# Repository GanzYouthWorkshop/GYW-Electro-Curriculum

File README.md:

# GYW-Electro-Curriculum
Electronic curriculum and oher simple circuits for the Ganz Youth Workshop electric group.

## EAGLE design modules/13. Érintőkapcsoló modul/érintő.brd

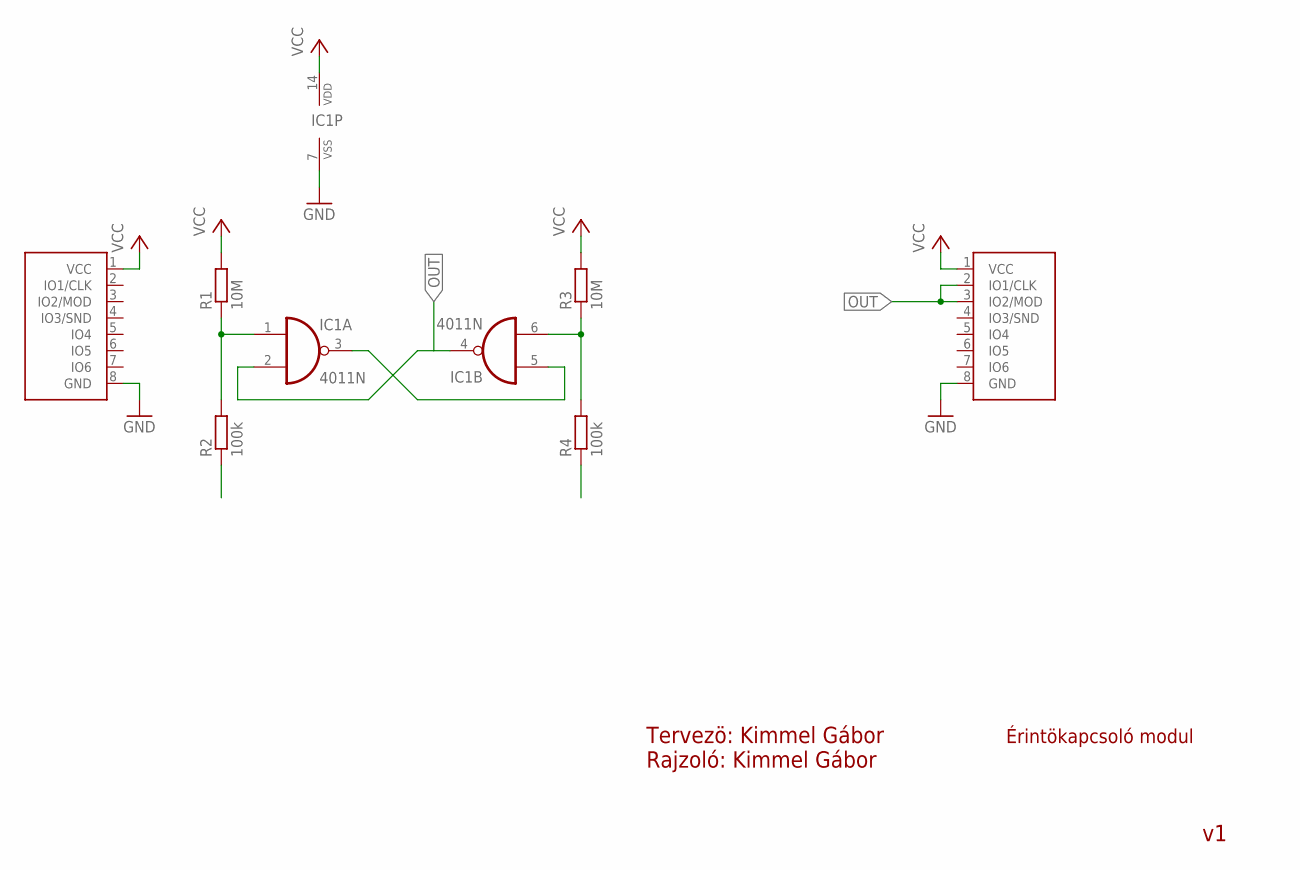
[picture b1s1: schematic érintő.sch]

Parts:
IC1: 4011N; DIL14
R1, R3: 10M; 0309/12
R2, R4: 100k; 0309/12
U$1: GANZ-CONNECTOR; FE08W
U$2: GANZ-CONNECTOR-OUT; MA08-1W

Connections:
GND: IC1.7 (VSS), U$1.8 (GND), U$2.8 (GND)
unnamed: IC1.3 (O), IC1.5 (I0)
unnamed: IC1.1 (I0), R1.1, R2.2
unnamed: IC1.6 (I1), R3.1, R4.2
OUT: IC1.2 (I1), IC1.4 (O), U$2.2 (IO1/CLK), U$2.3 (IO2/MOD)
PAD1: R2.1
PAD2: R4.1
VCC: IC1.14 (VDD), R1.2, R3.2, U$1.1 (VCC), U$2.1 (VCC)

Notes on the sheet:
Érintökapcsoló modul
Tervezö: Kimmel Gábor Rajzoló: Kimmel Gábor

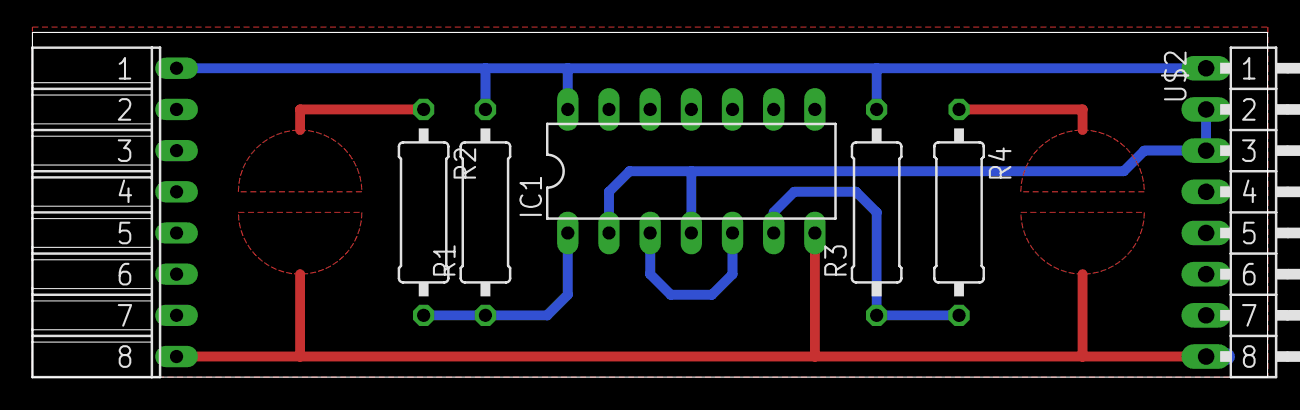
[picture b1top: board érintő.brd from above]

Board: 2 copper layers, 76.2 x 21.3 mm, 7 parts (0 on the bottom side), 6 nets.

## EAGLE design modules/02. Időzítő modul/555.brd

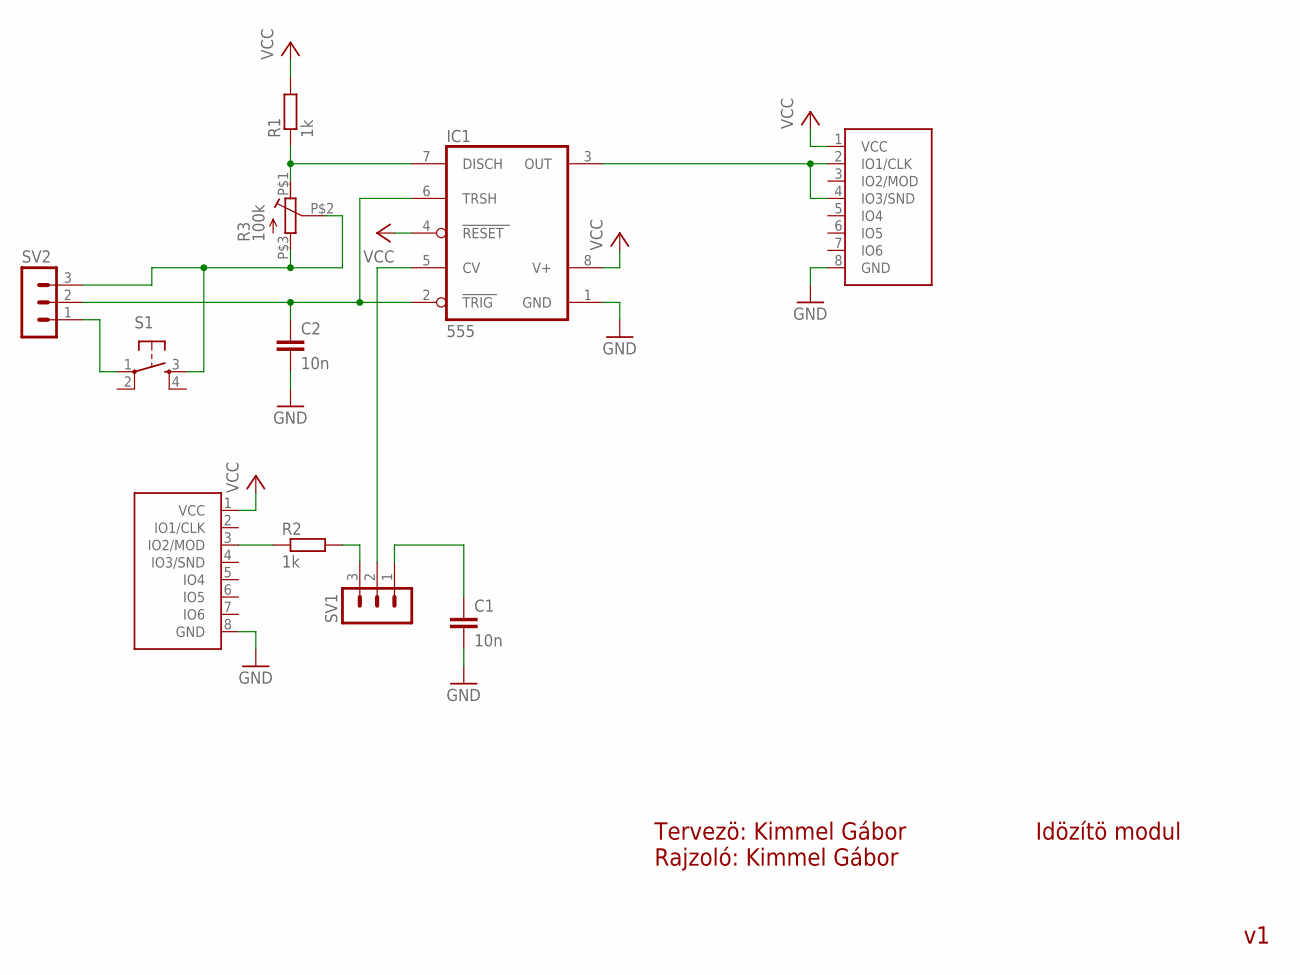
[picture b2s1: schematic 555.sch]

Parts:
C1, C2: 10n; C075-032X103
IC1: 555; DIL08
R1, R2: 1k; 0309/12
R3: 100k; GANZ_POT
S1: TAC_SWITCHPTH; TACTILE-PTH
SV1, SV2: MA03-1
U$2: ó; FE08W
U$3: GANZ-CONNECTOR-OUT; MA08-1W

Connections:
GND: C1.2, C2.2, IC1.1 (GND), U$2.8 (GND), U$3.8 (GND)
unnamed: IC1.7 (DISCH), R1.1, R3.P$1 (A)
unnamed: R3.P$2 (S), R3.P$3 (E), S1.3, SV2.3
unnamed: IC1.3 (OUT), U$3.2 (IO1/CLK), U$3.4 (IO3/SND)
unnamed: IC1.5 (CV), SV1.2
unnamed: S1.1, SV2.1
unnamed: C1.1, SV1.1
unnamed: R2.1, U$2.3 (IO2/MOD)
unnamed: C2.1, IC1.2 (TRIG), IC1.6 (TRSH), SV2.2
unnamed: R2.2, SV1.3
VCC: IC1.4 (RESET), IC1.8 (V+), R1.2, U$2.1 (VCC), U$3.1 (VCC)

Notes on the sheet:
Idözítö modul
Tervezö: Kimmel Gábor Rajzoló: Kimmel Gábor

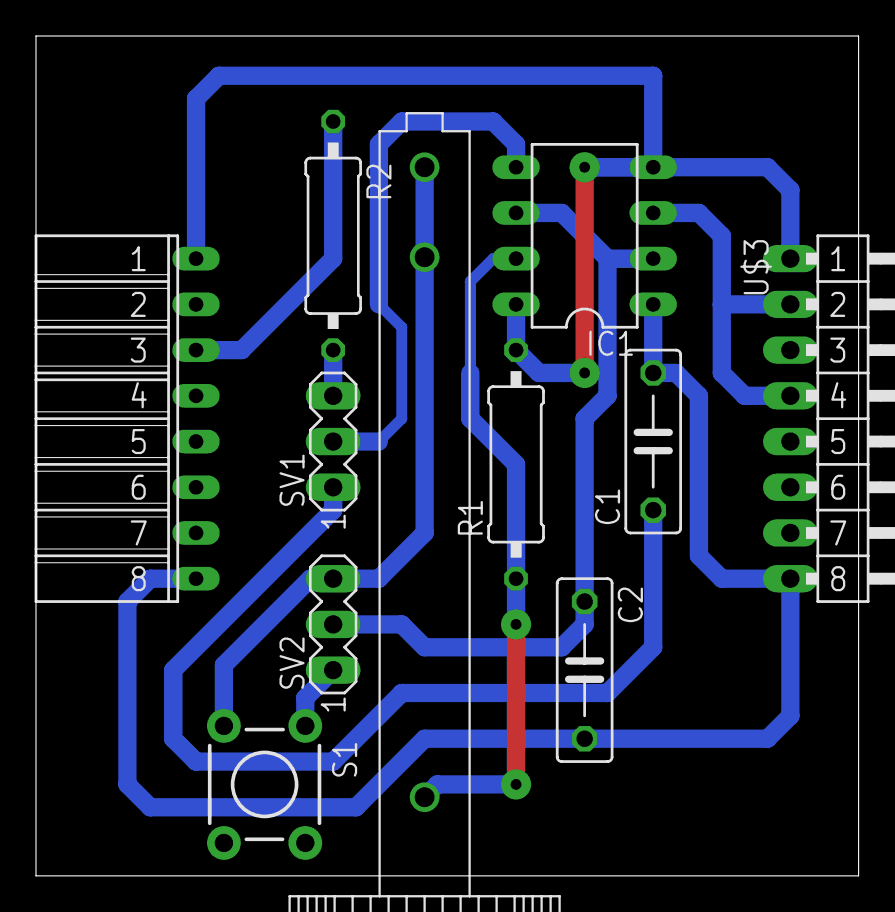
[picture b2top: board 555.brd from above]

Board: 2 copper layers, 45.7 x 46.7 mm, 11 parts (0 on the bottom side), 11 nets.

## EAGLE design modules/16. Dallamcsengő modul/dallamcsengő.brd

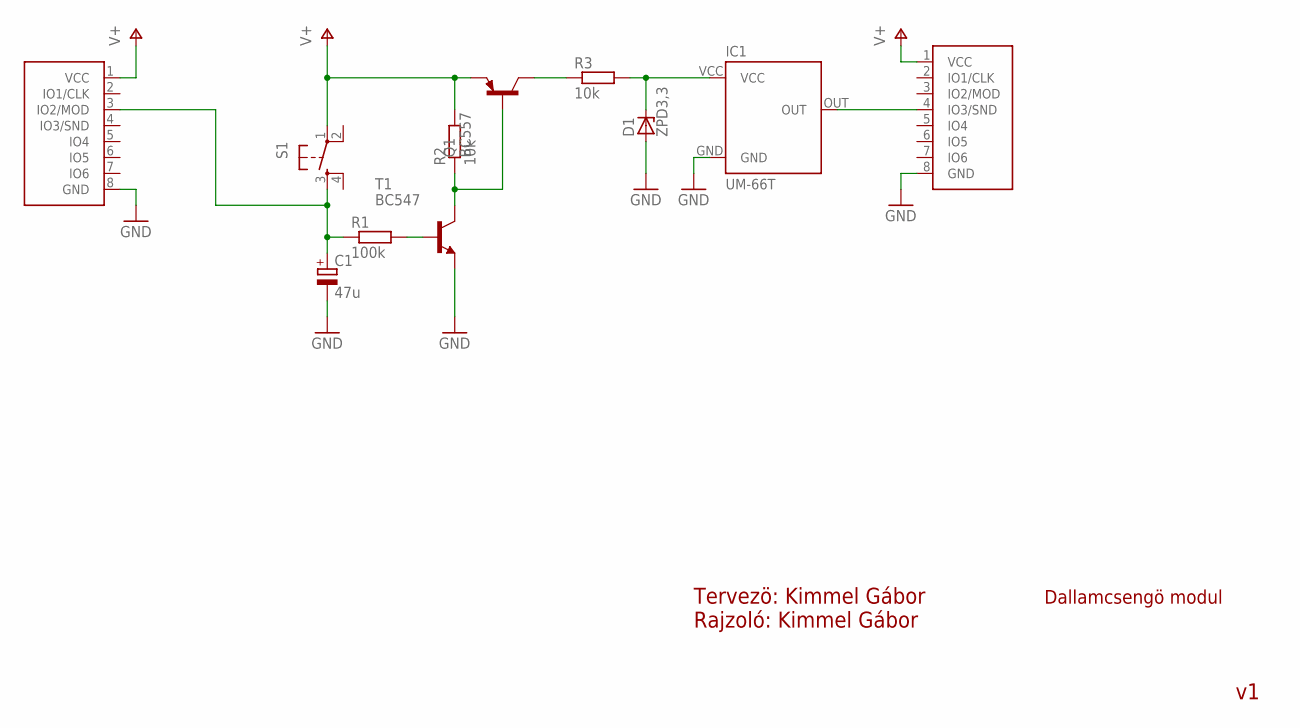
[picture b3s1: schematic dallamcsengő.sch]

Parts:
C1: 47u; E5-8,5
D1: ZPD3,3; DO35Z10
IC1: UM-66T; TO92-DCS
Q1: BC557; TO92
R1: 100k; 0309/12
R2, R3: 10k; 0309/12
S1: TAC_SWITCHPTH; TACTILE-PTH
T1: BC547; TO92
U$1: GANZ-CONNECTOR; FE08W
U$2: GANZ-CONNECTOR-OUT; MA08-1W

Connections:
GND: C1.-, D1.A, IC1.GND, T1.1 (E), U$1.8 (GND), U$2.8 (GND)
unnamed: C1.+, R1.1, S1.3, U$1.3 (IO2/MOD)
unnamed: R1.2, T1.2 (B)
unnamed: Q1.2 (B), R2.1, T1.3 (C)
unnamed: D1.C, IC1.VCC, R3.2
unnamed: IC1.OUT, U$2.4 (IO3/SND)
unnamed: Q1.3 (C), R3.1
V+: Q1.1 (E), R2.2, S1.1, U$1.1 (VCC), U$2.1 (VCC)

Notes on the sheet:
Dallamcsengö modul
Tervezö: Kimmel Gábor Rajzoló: Kimmel Gábor

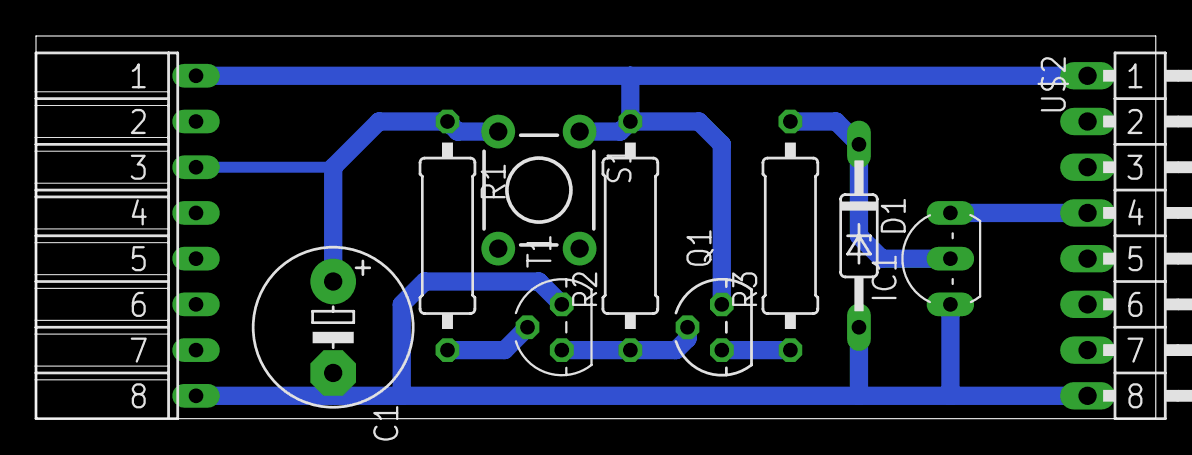
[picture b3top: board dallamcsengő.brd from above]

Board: 2 copper layers, 62.2 x 21.3 mm, 11 parts (0 on the bottom side), 8 nets.

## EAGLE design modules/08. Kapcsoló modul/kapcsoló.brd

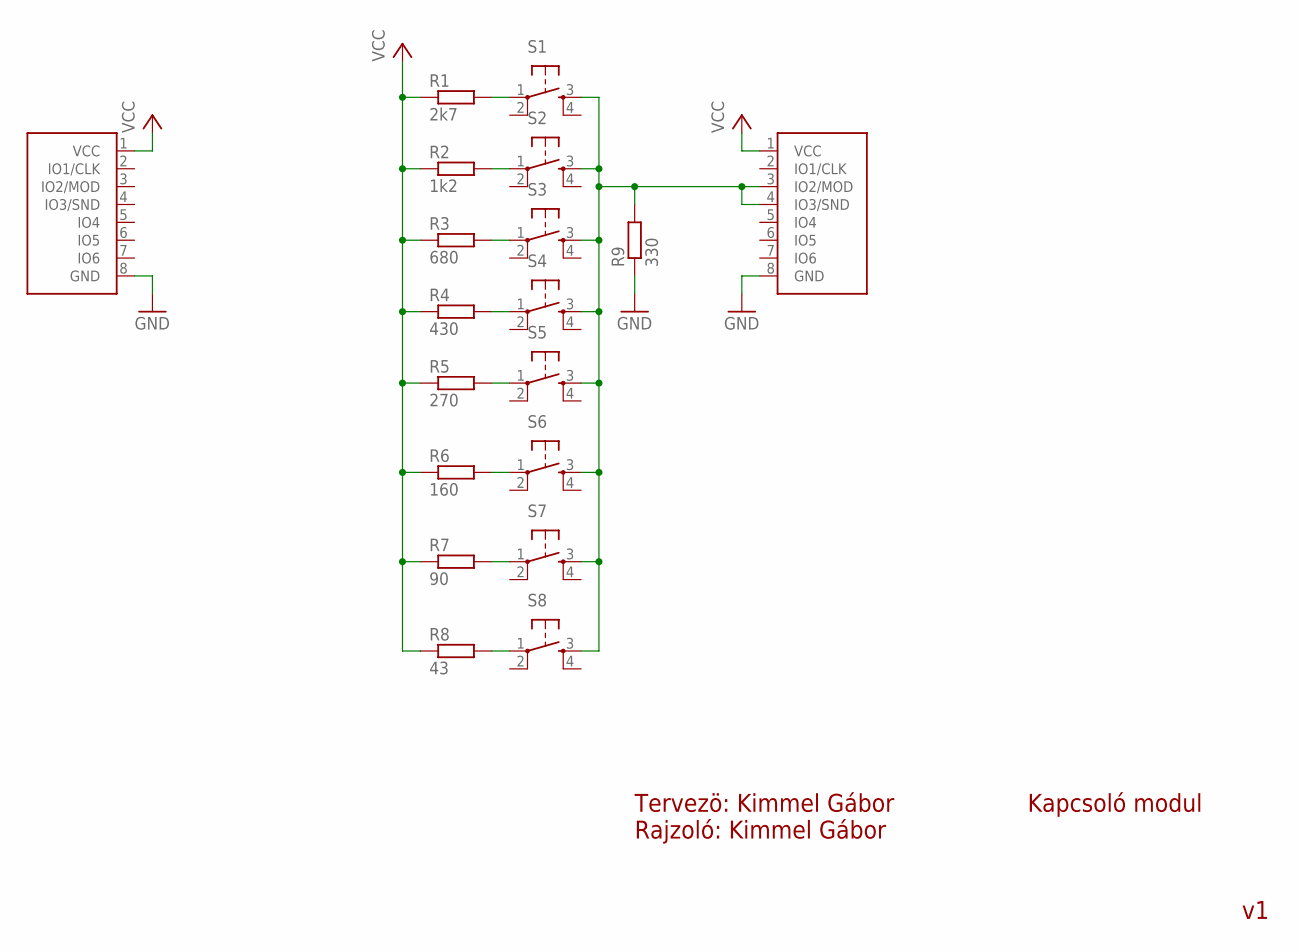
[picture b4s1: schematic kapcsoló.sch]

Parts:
R1: 2k7; 0309/12
R2: 1k2; 0309/12
R3: 680; 0309/12
R4: 430; 0309/12
R5: 270; 0309/12
R6: 160; 0309/12
R7: 90; 0309/12
R8: 43; 0309/12
R9: 330; 0309/12
S1, S2, S3, S4, S5, S6, S7, S8: TAC_SWITCHPTH; TACTILE-PTH
U$1: GANZ-CONNECTOR-OUT; MA08-1W
U$2: GANZ-CONNECTOR; FE08W

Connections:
GND: R9.1, U$1.8 (GND), U$2.8 (GND)
unnamed: R8.2, S8.1
unnamed: R7.2, S7.1
unnamed: R6.2, S6.1
unnamed: R5.2, S5.1
unnamed: R4.2, S4.1
unnamed: R3.2, S3.1
unnamed: R2.2, S2.1
unnamed: R1.2, S1.1
unnamed: R9.2, S1.3, S2.3, S3.3, S4.3, S5.3, S6.3, S7.3, S8.3, U$1.3 (IO2/MOD), U$1.4 (IO3/SND)
VCC: R1.1, R2.1, R3.1, R4.1, R5.1, R6.1, R7.1, R8.1, U$1.1 (VCC), U$2.1 (VCC)

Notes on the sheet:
Kapcsoló modul
Tervezö: Kimmel Gábor Rajzoló: Kimmel Gábor

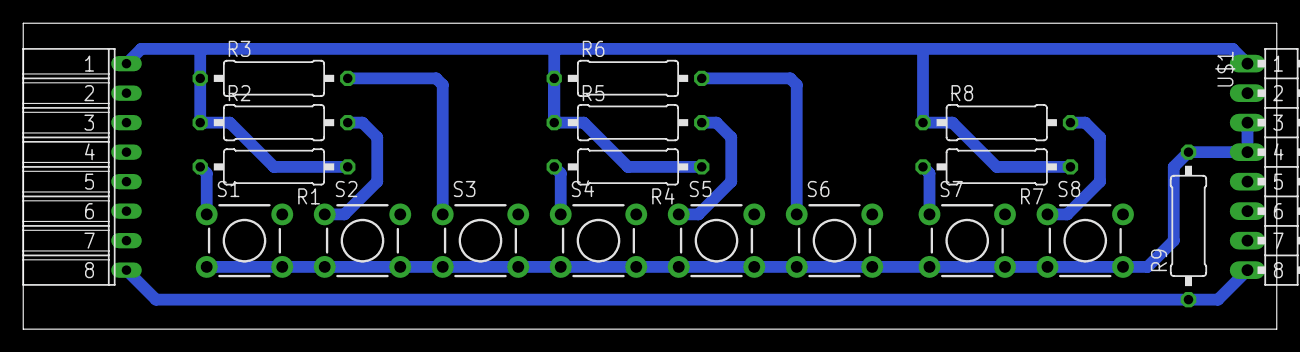
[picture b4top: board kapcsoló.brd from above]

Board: 2 copper layers, 107.9 x 26.3 mm, 19 parts (0 on the bottom side), 11 nets.

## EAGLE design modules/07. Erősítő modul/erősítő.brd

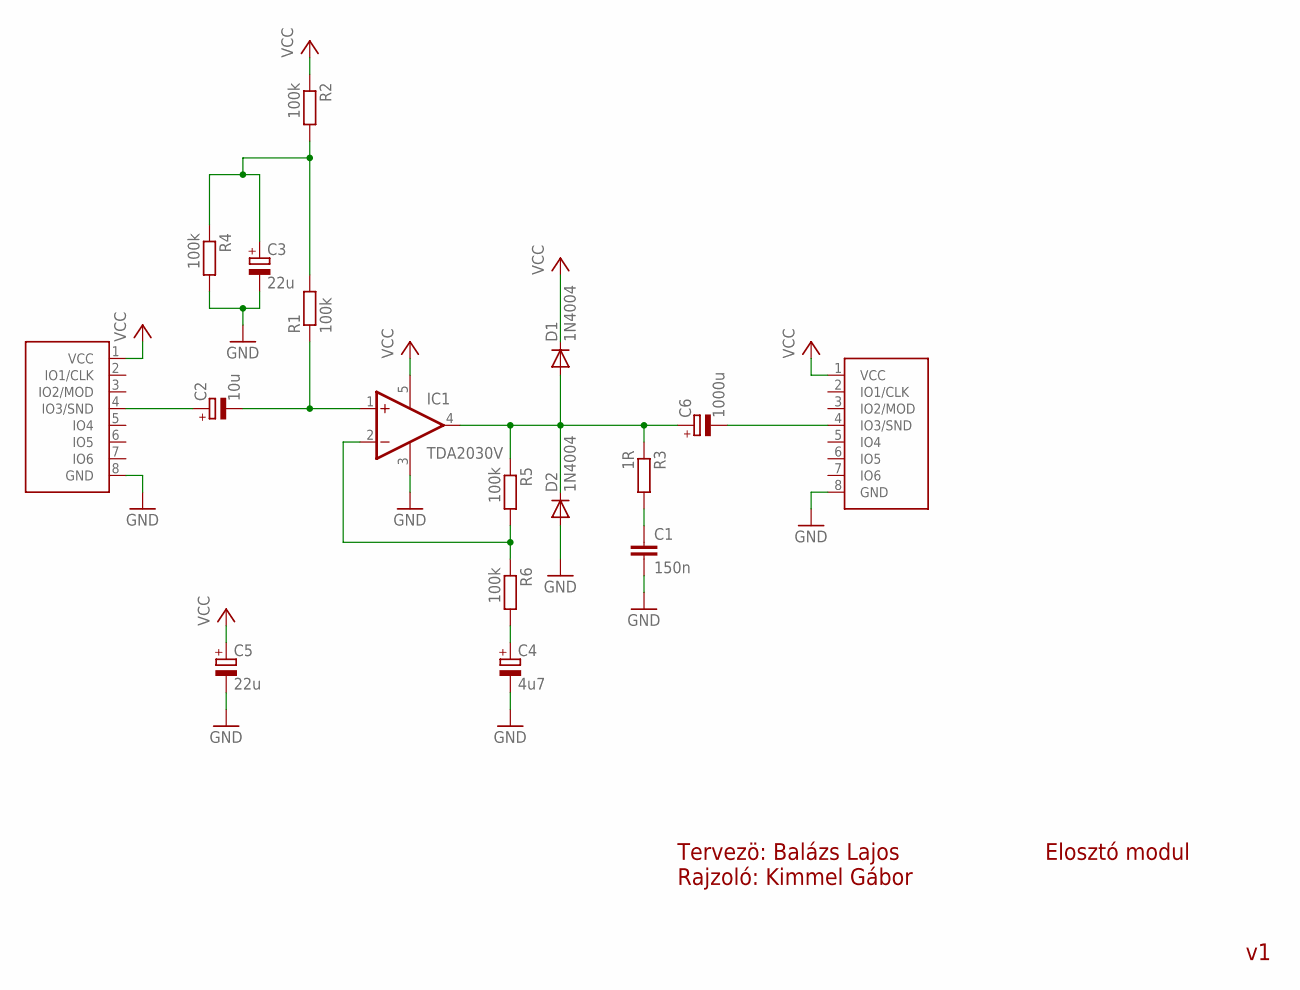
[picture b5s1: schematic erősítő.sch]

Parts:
C1: 150n; C075-032X103
C2: 10u; E2,5-7
C3, C5: 22u; E2,5-7
C4: 4u7; E2,5-7
C6: 1000u; E3,5-8
D1, D2: 1N4004; DO41-10
IC1: TDA2030V; CB360
R1, R2, R4, R5, R6: 100k; 0309/12
R3: 1R; 0309/12
U$1: GANZ-CONNECTOR; FE08W
U$2: GANZ-CONNECTOR-OUT; MA08-1W

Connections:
GND: C1.2, C3.-, C4.-, C5.-, D2.A, IC1.3 (GND), R4.2, U$1.8 (GND), U$2.8 (GND)
unnamed: C6.+, D1.A, D2.C, IC1.4 (OUT), R3.1, R5.1
unnamed: C3.+, R1.2, R2.2, R4.1
unnamed: C2.-, IC1.1 (+IN), R1.1
unnamed: C2.+, U$1.4 (IO3/SND)
unnamed: IC1.2 (-IN), R5.2, R6.1
unnamed: C4.+, R6.2
unnamed: C1.1, R3.2
unnamed: C6.-, U$2.4 (IO3/SND)
VCC: C5.+, D1.C, IC1.5 (V+), R2.1, U$1.1 (VCC), U$2.1 (VCC)

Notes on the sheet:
Elosztó modul
Tervezö: Balázs Lajos Rajzoló: Kimmel Gábor

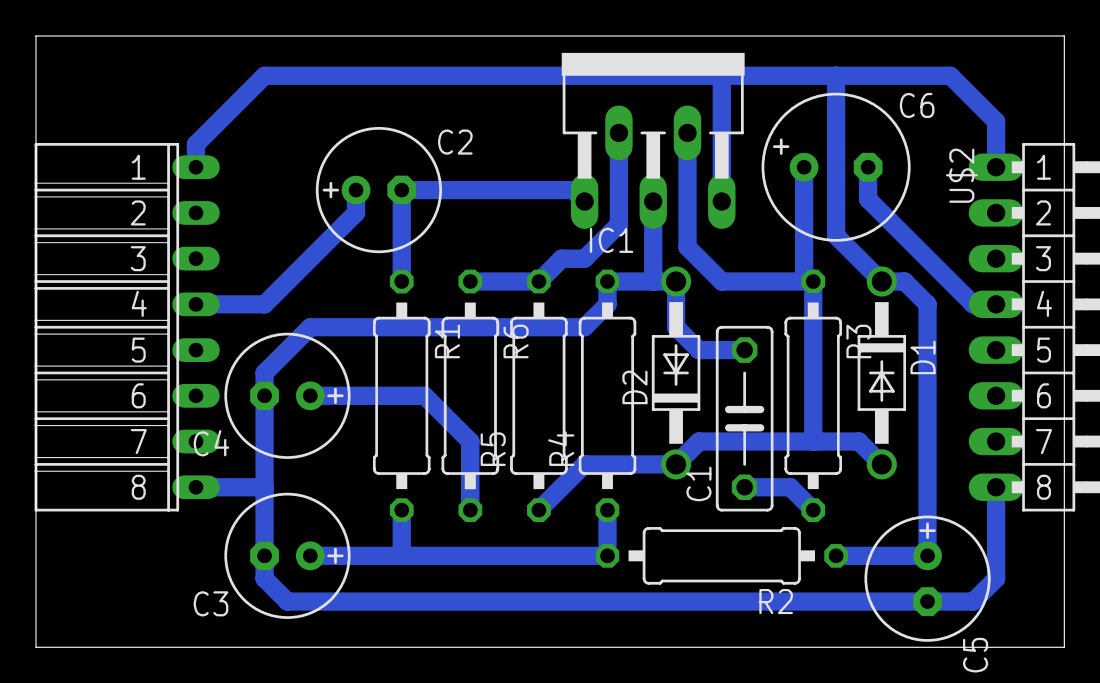
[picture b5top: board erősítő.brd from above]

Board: 2 copper layers, 57.1 x 34.0 mm, 17 parts (0 on the bottom side), 10 nets.

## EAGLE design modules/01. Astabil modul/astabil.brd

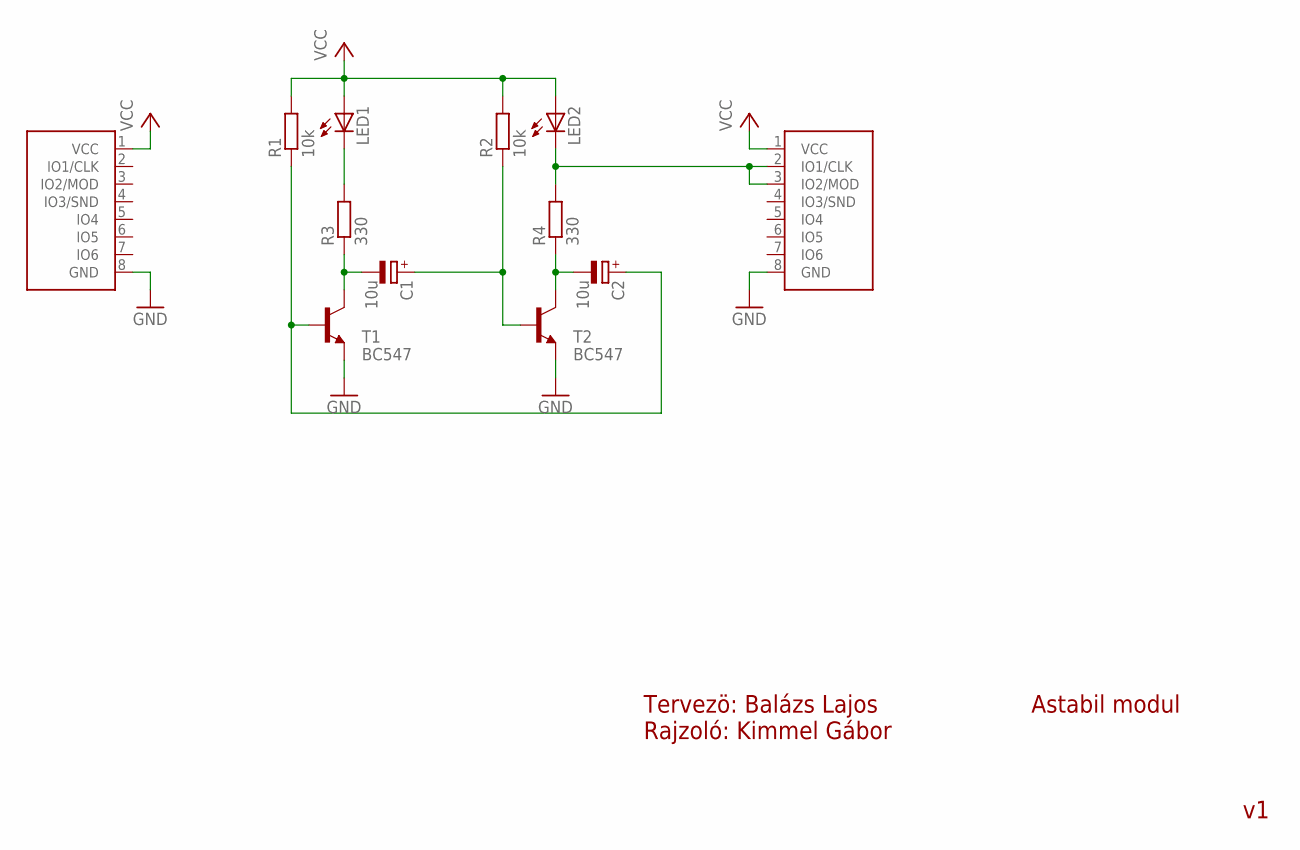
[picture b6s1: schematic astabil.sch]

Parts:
C1, C2: 10u; E3,5-8
LED1, LED2: LED5MM
R1, R2: 10k; 0207/10
R3, R4: 330; 0207/10
T1, T2: BC547; TO92-CBE
U$1: GANZ-CONNECTOR; FE08W
U$2: GANZ-CONNECTOR-OUT; MA08-1W

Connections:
GND: T1.E, T2.E, U$1.8 (GND), U$2.8 (GND)
unnamed: C2.+, R1.1, T1.B
unnamed: C1.+, R2.1, T2.B
unnamed: C1.-, R3.1, T1.C
unnamed: LED1.K (C), R3.2
unnamed: C2.-, R4.1, T2.C
unnamed: LED2.K (C), R4.2, U$2.2 (IO1/CLK), U$2.3 (IO2/MOD)
VCC: LED1.A, LED2.A, R1.2, R2.2, U$1.1 (VCC), U$2.1 (VCC)

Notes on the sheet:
Astabil modul
Tervezö: Balázs Lajos Rajzoló: Kimmel Gábor

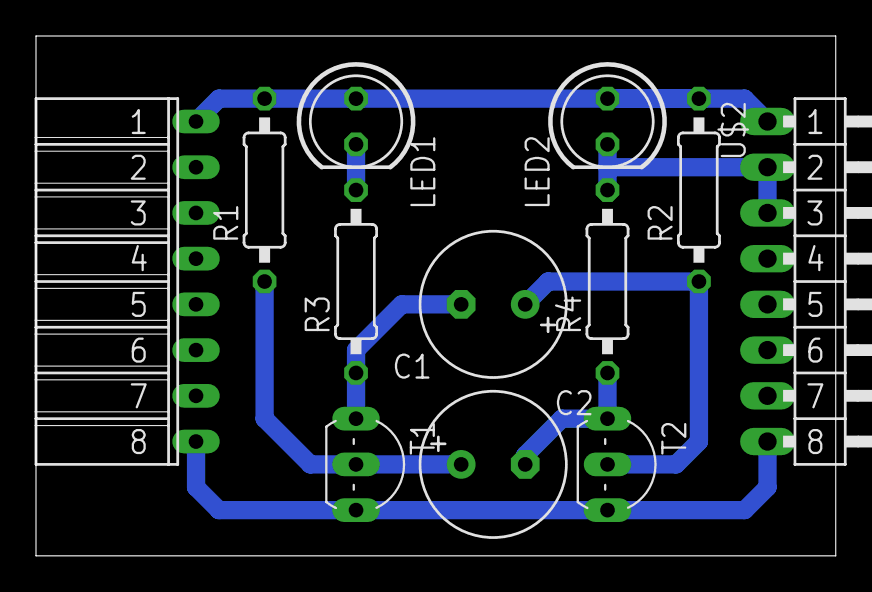
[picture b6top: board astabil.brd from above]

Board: 2 copper layers, 44.4 x 28.9 mm, 12 parts (0 on the bottom side), 8 nets.

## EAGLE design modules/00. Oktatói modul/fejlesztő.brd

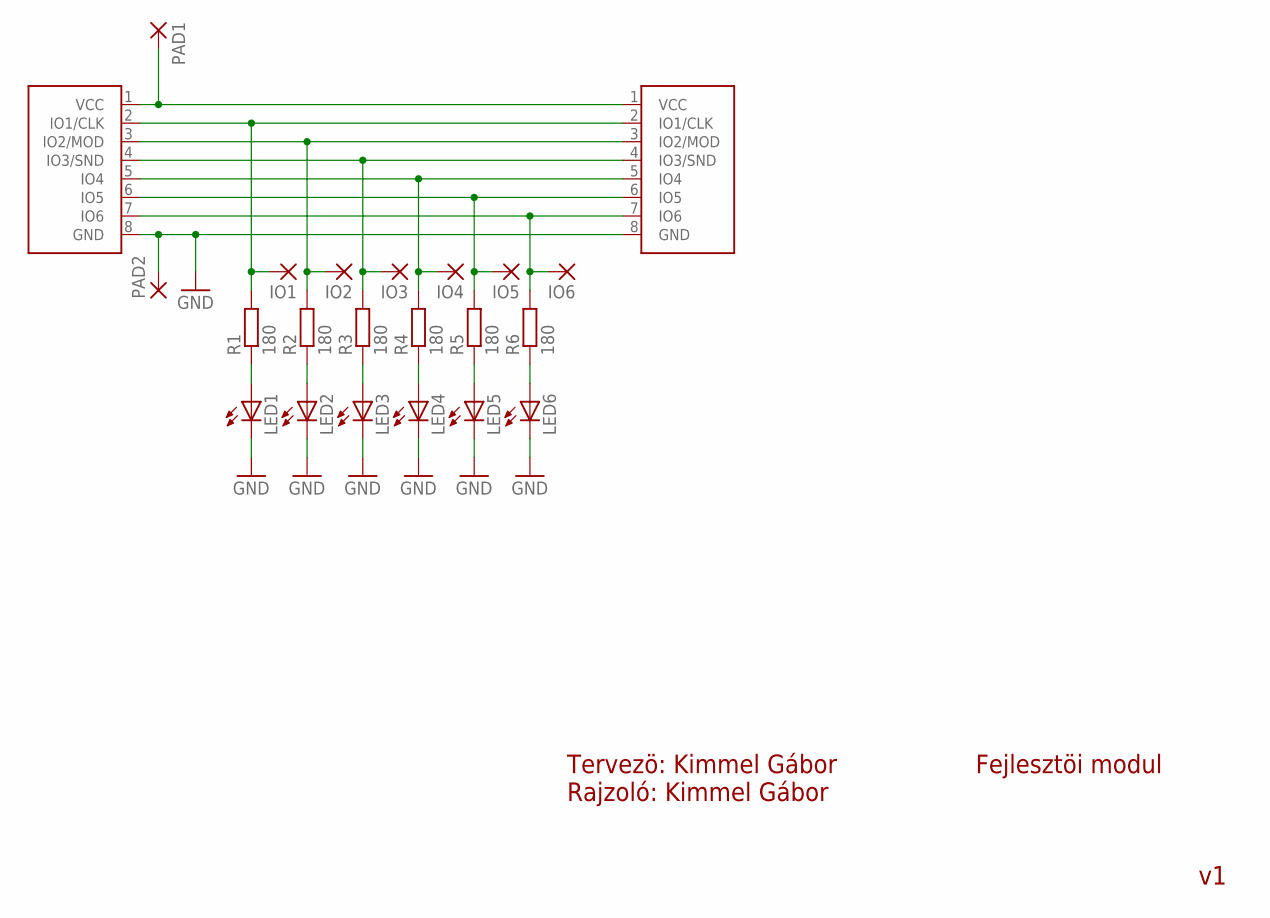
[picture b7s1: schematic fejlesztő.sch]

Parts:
IO1, IO2, IO3, IO4, IO5, IO6: 2,15/1,0
LED1, LED2, LED3, LED4, LED5, LED6: LED5MM
PAD1, PAD2: 3,17/1,1
R1, R2, R3, R4, R5, R6: 180; 0207/10
U$1: GANZ-CONNECTOR; FE08W
U$2: GANZ-CONNECTOR-OUT; MA08-1W

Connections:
GND: LED1.K (C), LED2.K (C), LED3.K (C), LED4.K (C), LED5.K (C), LED6.K (C), PAD2.1, U$1.8 (GND), U$2.8 (GND)
unnamed: PAD1.1, U$1.1 (VCC), U$2.1 (VCC)
unnamed: LED1.A, R1.1
unnamed: IO1.1, R1.2, U$1.2 (IO1/CLK), U$2.2 (IO1/CLK)
unnamed: LED2.A, R2.1
unnamed: IO2.1, R2.2, U$1.3 (IO2/MOD), U$2.3 (IO2/MOD)
unnamed: LED3.A, R3.1
unnamed: IO3.1, R3.2, U$1.4 (IO3/SND), U$2.4 (IO3/SND)
unnamed: LED4.A, R4.1
unnamed: IO4.1, R4.2, U$1.5 (IO4), U$2.5 (IO4)
unnamed: LED5.A, R5.1
unnamed: IO5.1, R5.2, U$1.6 (IO5), U$2.6 (IO5)
unnamed: LED6.A, R6.1
unnamed: IO6.1, R6.2, U$1.7 (IO6), U$2.7 (IO6)

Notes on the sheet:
Fejlesztöi modul
Tervezö: Kimmel Gábor Rajzoló: Kimmel Gábor

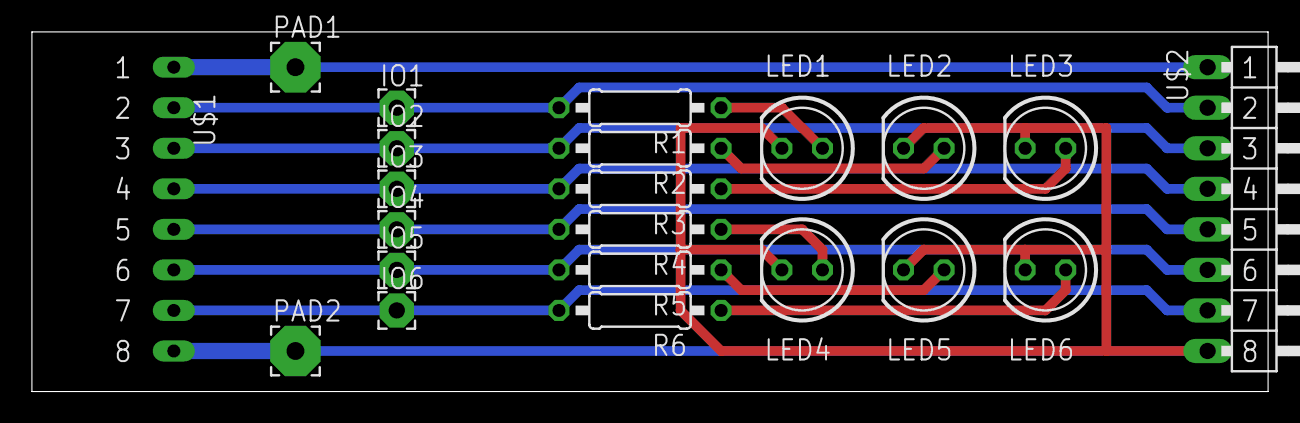
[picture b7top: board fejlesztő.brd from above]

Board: 2 copper layers, 77.5 x 22.5 mm, 22 parts (0 on the bottom side), 14 nets.

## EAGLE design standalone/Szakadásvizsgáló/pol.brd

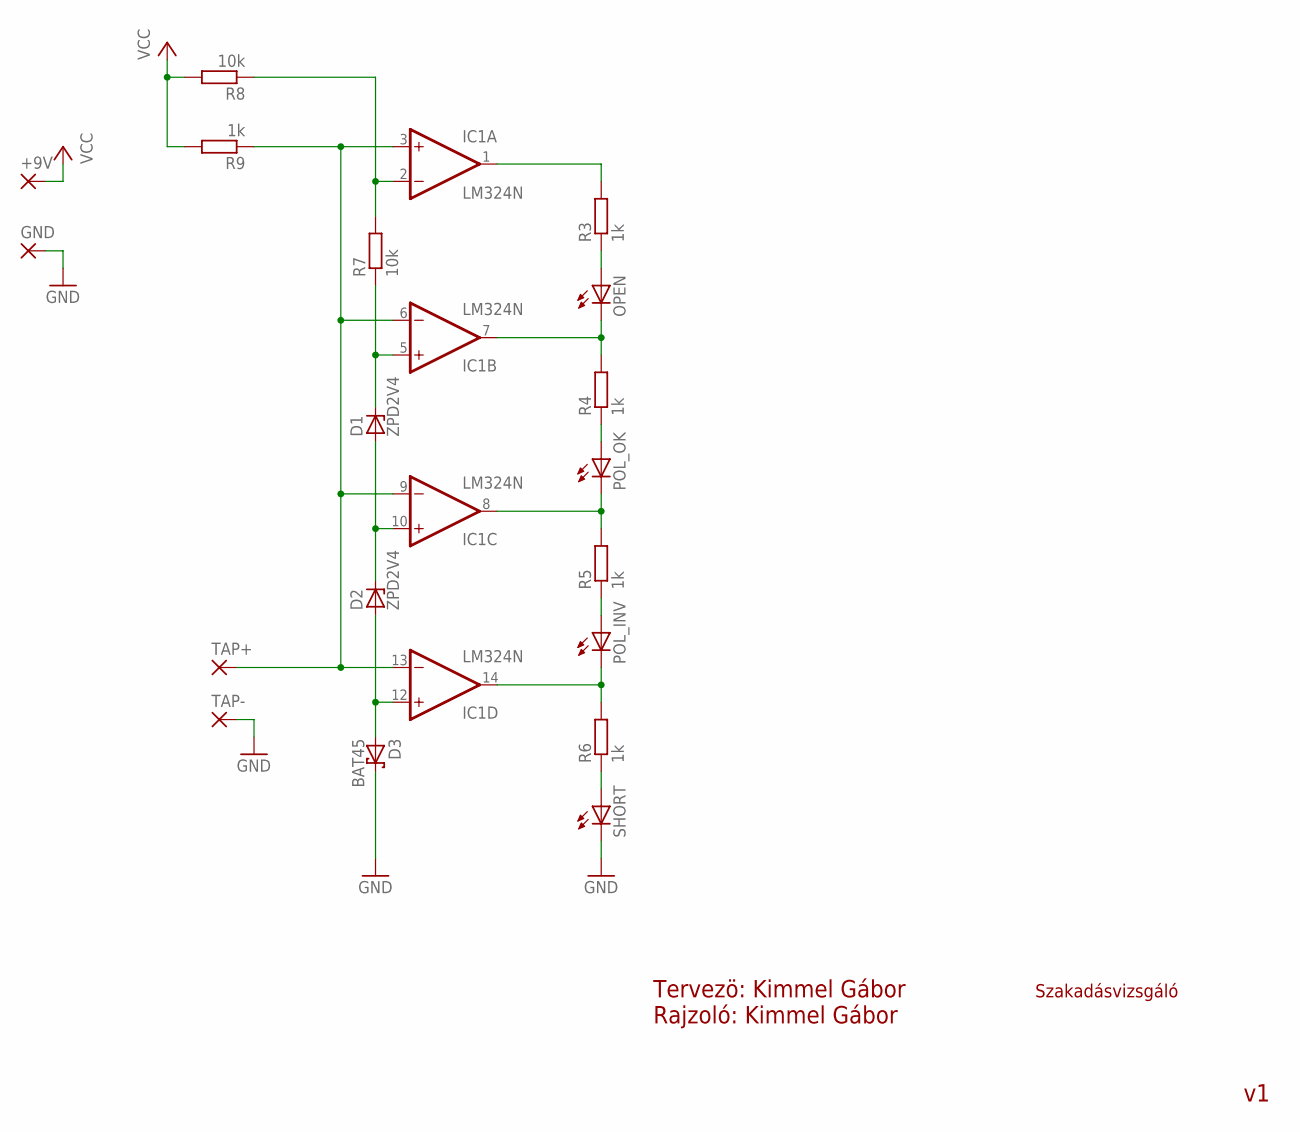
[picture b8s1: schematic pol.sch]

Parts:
+9V: 2,54/1,0
D1, D2: ZPD2V4; DO35Z10
D3: BAT45; DO35-10
GND: 2,54/1,0
IC1: LM324N; DIL14
OPEN: LED5MM
POL_INV: LED5MM
POL_OK: LED5MM
R3, R4, R5, R6, R9: 1k; 0309/12
R7, R8: 10k; 0309/12
SHORT: LED5MM
TAP+: 2,54/1,0
TAP-: 2,54/1,0

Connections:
GND: D3.C, GND.1, SHORT.K (C), TAP-.1
unnamed: IC1.14 (OUT), POL_INV.K (C), R6.2
unnamed: R6.1, SHORT.A
unnamed: POL_INV.A, R5.1
unnamed: IC1.8 (OUT), POL_OK.K (C), R5.2
unnamed: POL_OK.A, R4.1
unnamed: IC1.7 (OUT), OPEN.K (C), R4.2
unnamed: OPEN.A, R3.1
unnamed: IC1.1 (OUT), R3.2
unnamed: D2.A, D3.A, IC1.12 (+IN)
unnamed: D1.A, D2.C, IC1.10 (+IN)
unnamed: D1.C, IC1.5 (+IN), R7.1
unnamed: IC1.2 (-IN), R7.2, R8.1
unnamed: IC1.3 (+IN), IC1.6 (-IN), IC1.9 (-IN), IC1.13 (-IN), R9.1, TAP+.1
V+: IC1.4 (V+)
V-: IC1.11 (V-)
VCC: +9V.1, R8.2, R9.2

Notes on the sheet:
Szakadásvizsgáló
Tervezö: Kimmel Gábor Rajzoló: Kimmel Gábor

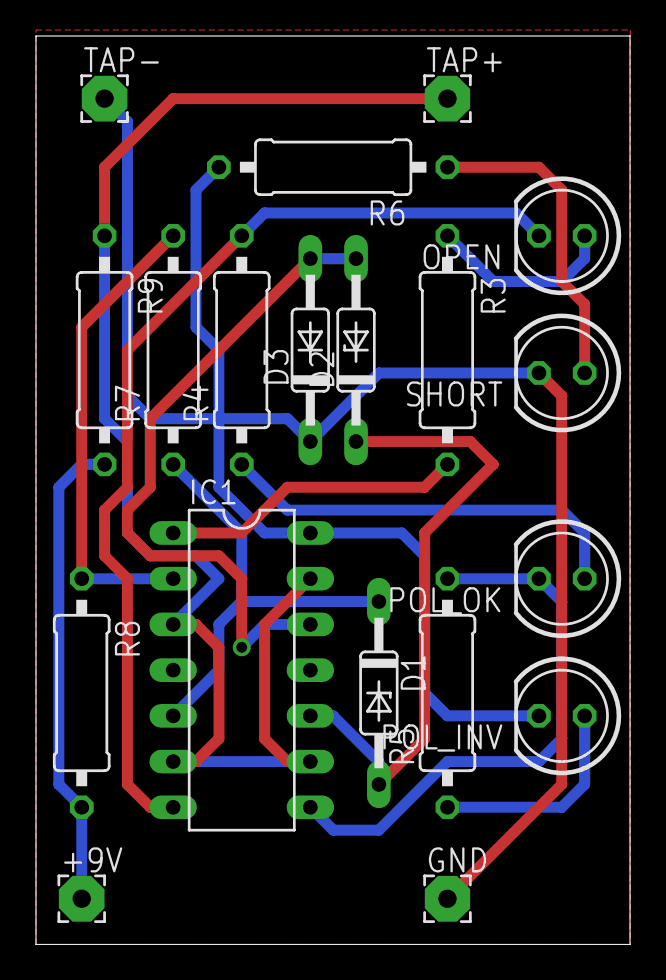
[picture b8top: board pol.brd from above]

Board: 2 copper layers, 33.0 x 50.5 mm, 19 parts (0 on the bottom side), 15 nets.

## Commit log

2019-06-30 Common EAGLE library, Astable module added
2019-06-30 Added descriptions and standalone workshop astable
2019-06-30 Added 555 module
2019-06-30 More descriptions, 3,5mm module
2019-06-30 Added more modules
2019-07-01 Removed ignore file
2019-07-02 Added modules
2019-07-03 Added standalone circuit and utility drawing
2019-07-04 Added 2 standalone projects
2019-08-08 Added most CAM files

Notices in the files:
parts and their libraries:
SparkFun-Electromechanical: Licensing: Creative Commons ShareAlike 4.0 International - https://creativecommons.org/licenses/by-sa/4.0
